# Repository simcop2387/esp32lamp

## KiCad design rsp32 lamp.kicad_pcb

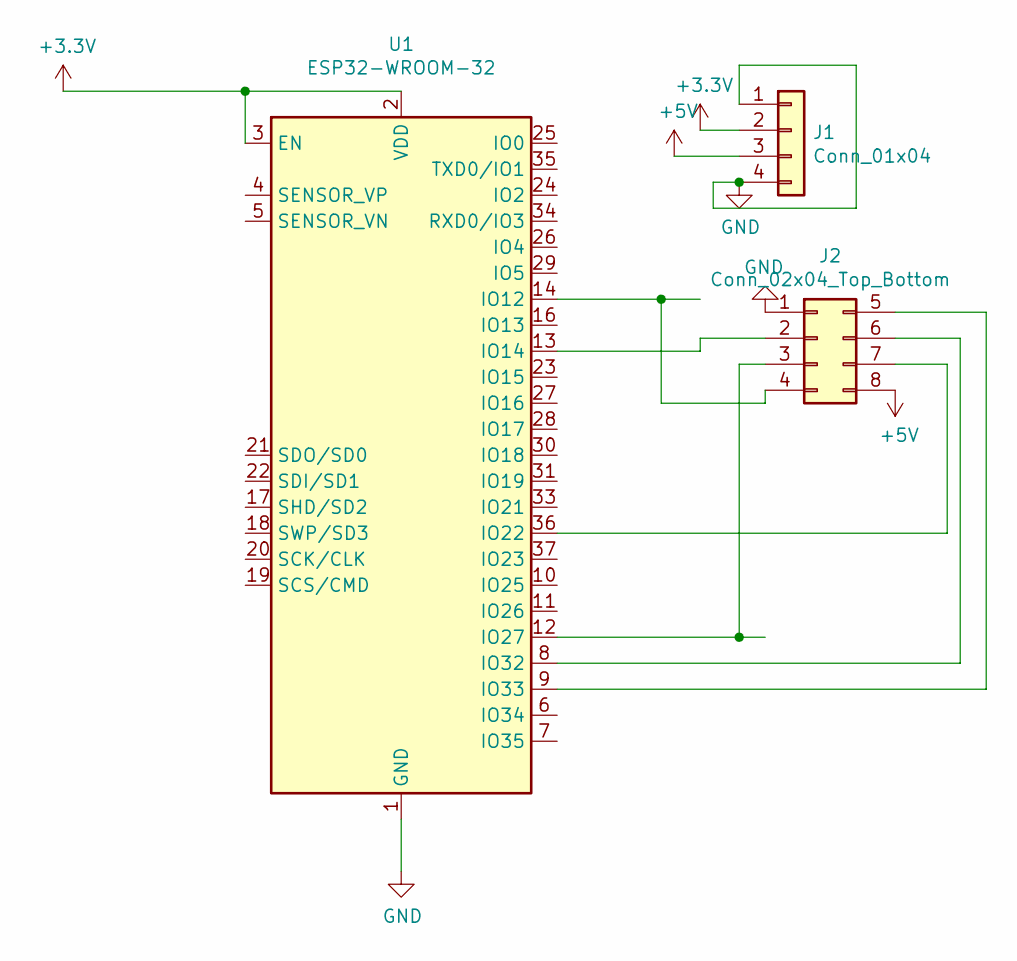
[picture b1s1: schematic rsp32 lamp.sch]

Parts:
J1: Conn_01x04; PinHeader_1x04_P2.54mm_Vertical
J2: Conn_02x04_Top_Bottom; PinHeader_1x08_P2.54mm_Vertical
U1: ESP32-WROOM-32

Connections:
+3V3: J1.2, U1.2 (VDD), U1.3 (EN)
+5V: J1.3, J2.8
GND: J1.1, J1.4, J2.1, U1.1 (GND), U1.15 (GND), U1.38 (GND), U1.39 (GND)
unnamed: J2.2, U1.13 (IO14)
unnamed: J2.3, U1.12 (IO27)
unnamed: J2.4, U1.14 (IO12)
unnamed: J2.5, U1.9 (IO33)
unnamed: J2.6, U1.8 (IO32)
unnamed: J2.7, U1.36 (IO22)

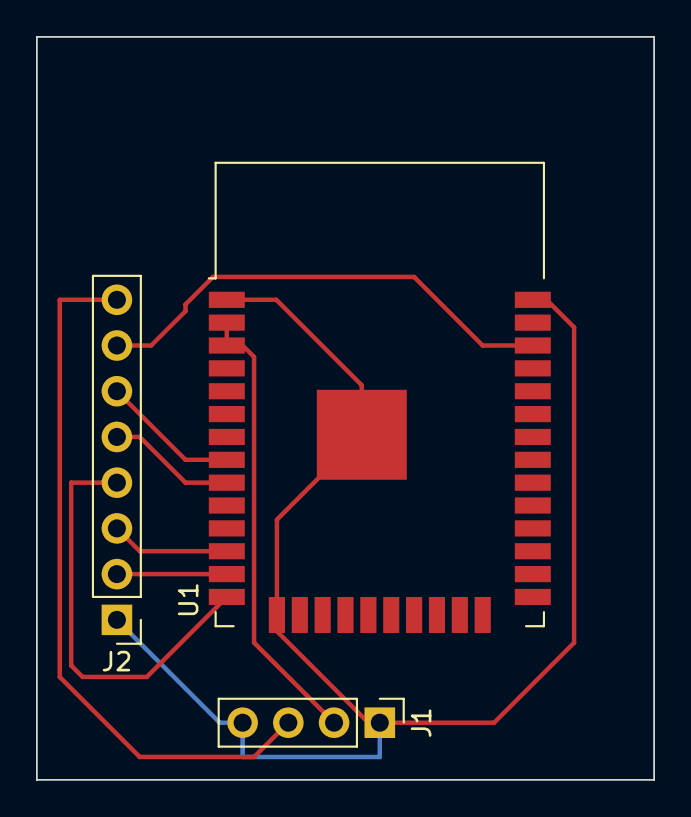
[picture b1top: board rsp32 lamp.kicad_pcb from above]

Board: 2 copper layers, 34.3 x 41.3 mm, 3 parts (0 on the bottom side), 9 nets.

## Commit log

2021-09-10 breakout
2021-09-10 image
2021-09-10 code
